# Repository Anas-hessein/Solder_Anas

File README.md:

# solder_sussy
A light-sensitive owl PCB with glowing LED eyes (photoresistor-controlled) and a button that makes its tiny DC motor "wings" buzz to life, like it’s trying to fly off your desk.

## Schematic

## PCB

## Simulation

- https://tinyurl.com/2ctncmjq

## BOM
- 2 LEDs
- 1 Photoresistor
- 1 Battery holder
- 1 Button
- 1 Vibration motors

Made by @Anaskiiled on slack :]

Made as a part of http://solder.hackclub.com/!

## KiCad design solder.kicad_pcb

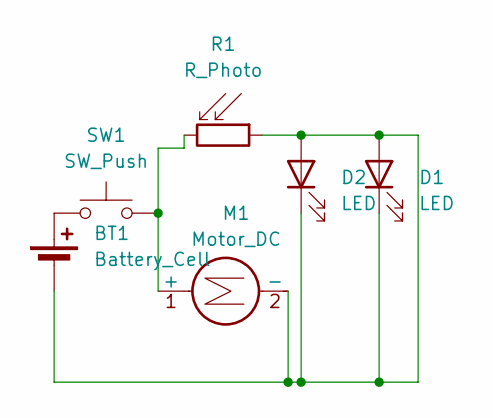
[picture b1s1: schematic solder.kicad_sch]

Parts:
BT1: Battery_Cell; BatteryHolder_Keystone_3034_1x20mm
D1, D2: LED; LED_D5.0mm
M1: Motor_DC; PinHeader_1x02_P2.54mm_Vertical
R1: R_Photo; R_LDR_5.1x4.3mm_P3.4mm_Vertical
SW1: SW_Push; SW_PUSH_6mm

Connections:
unnamed: BT1.1 (+), SW1.1
unnamed: BT1.2 (-), D1.1 (K), D1.2 (A), D2.1 (K), D2.2 (A), M1.2 (-), R1.1
unnamed: M1.1 (+), R1.2, SW1.2

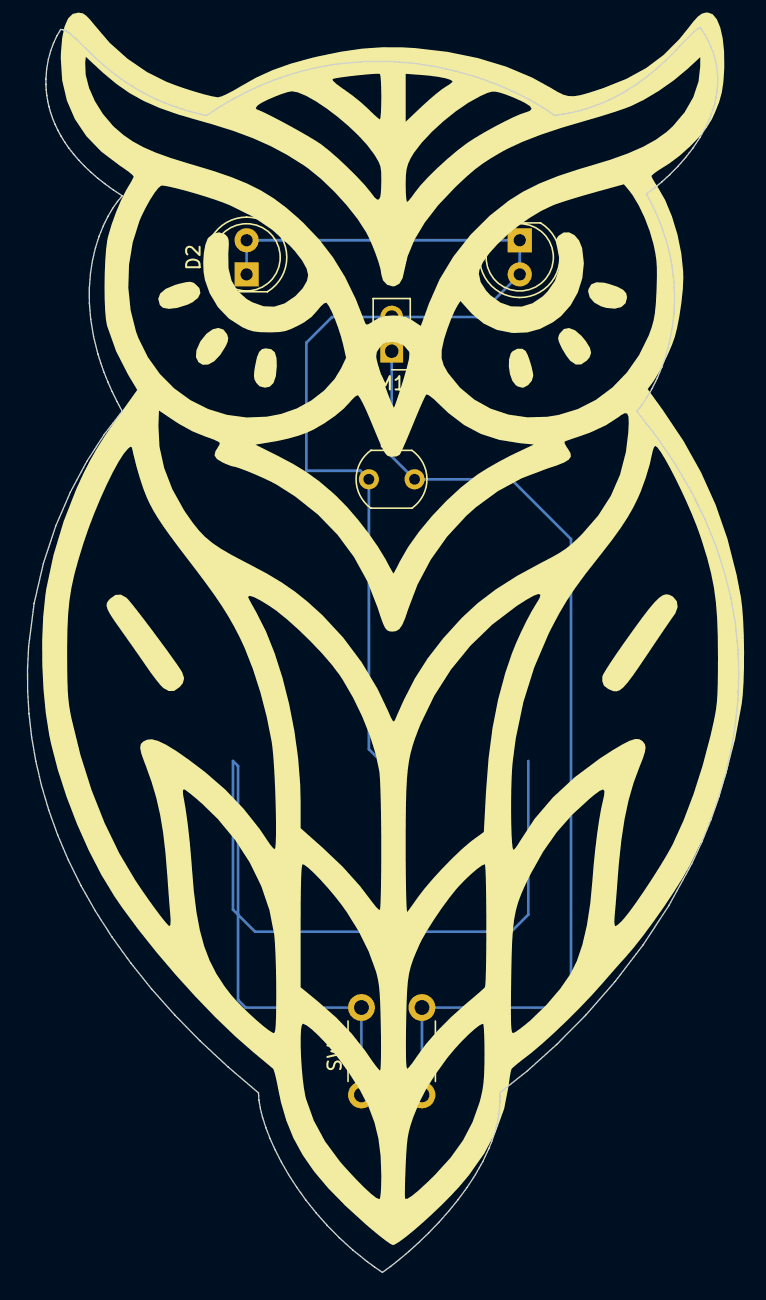
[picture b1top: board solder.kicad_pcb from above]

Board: 2 copper layers, 52.9 x 92.6 mm, 6 parts (1 on the bottom side), 3 nets.
